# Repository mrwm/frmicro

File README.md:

# frmicro
Pro Micro adaptation to a USB C male header
-

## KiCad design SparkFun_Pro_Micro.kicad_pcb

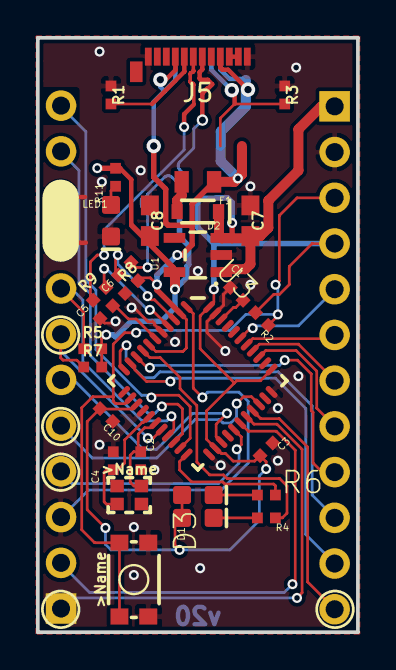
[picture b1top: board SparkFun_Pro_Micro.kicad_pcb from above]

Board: 2 copper layers, 17.8 x 33.0 mm, 35 parts (0 on the bottom side), 38 nets.

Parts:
C1, C3: 0.1uF; 0402-TIGHT
C2, C4: 22pF; 0402-TIGHT
C5, C6, C10: 1.0uF; 0402-TIGHT
C7, C8: 10uF; 0603
D1: Yellow; LED-0603
D2: 3A/10V/280mV; SOD-323
D3: GREEN; LED-0603
F1: 6V 0.5A; 0805
FRAME1: FRAME-LETTER; CREATIVE_COMMONS
J3, J4: CONN_12CASTLE; PinSocket_1x12_P2.54mm_Vertical
J5: USB_C5; USB_C_Plug_Molex_105444
JP4: JUMPER-SMT_3_1-NC_TRACE_SILK; SMT-JUMPER_3_1-NC_TRACE_SILK
LED1: RED; LED-0603
LOGO5: SPECIAL_INSTRUCTIONS-ORDERING; ORDERING_INSTRUCTIONS
R1, R3: 5.1k; 0402-TIGHT
R2: 10k; 0402-TIGHT
R4, R6, R11: 1k; 0402-TIGHT
R5, R7: 2.2k; 0402-TIGHT
R8, R9: 22OHM-0402T-1/16W-1%; 0402-TIGHT
S1: Reset; TACTILE_SWITCH_SMD_4.6X2.8MM
U1: 3.3V; SOT23-5
U3: 32U4; QFN-44-NOPAD_1_1-LESS_PASTE
U$3: OSHW-LOGOMINI; OSHW-LOGO-MINI
Y2: 16MHz; CRYSTAL-SMD-2.0X1.6MM

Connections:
3.3V: C8.2, JP4.1, R5.2, R7.2, R11.2, U1.5
/A0: J4.8, U3.36
/A1: J4.7, U3.37
/A2: J4.6, U3.38
/A3: J4.5, U3.39
/AREF: C1.2, U3.42
/D2/SDA: J3.8, R5.1, U3.19
/D3/SCL: J3.7, R7.1, U3.18
/D4: J3.6, U3.25
/D5: J3.5, U3.31
/D6: J3.4, U3.27
/D7: J3.3, U3.1
/D8: J3.2, U3.28
/D9: J3.1, U3.29
/D10: J4.12, U3.30
/D+: J5.A6, R9.1, R9.2, U3.4
/D-: J5.A7, R8.1, R8.2, U3.3
/MISO: J4.10, U3.11
/MOSI: J4.11, U3.10
/RAW: C7.2, D2.C, J4.1, JP4.3, U1.1, U1.3
/RESET: J4.3, R2.1, S1.3, S1.4, U3.13
/RXI: J3.11, U3.20
/SCK: J4.9, U3.9
/TXO: J3.12, U3.21
/UCAP: C5.2, U3.6
GND: C1.1, C2.2, C3.1, C4.2, C5.1, C6.1, C7.1, C8.1, C10.1, J3.9, J3.10, J4.2, J5.A1, J5.A12, J5.B1, J5.B12, LED1.C, R1.1, R3.1, S1.1, S1.2, U1.2, U3.5, U3.15, U3.23, U3.33, U3.35, U3.43
unnamed: C2.1, U3.17, Y2.3
unnamed: C4.1, U3.16, Y2.1
unnamed: D1.C, R4.2
unnamed: D2.A, F1.2
unnamed: D3.C, R6.2
unnamed: J5.A5, R1.2
unnamed: J5.B5, R3.2
unnamed: LED1.A, R11.1
unnamed: R4.1, U3.8
unnamed: R6.1, U3.22
VCC: C3.2, C10.2, D1.A, D3.A, J4.4, JP4.2, R2.2, U3.14, U3.24, U3.34, U3.44
V_USB: C6.2, F1.1, J5.A4, J5.A9, J5.B4, J5.B9, U3.2, U3.7

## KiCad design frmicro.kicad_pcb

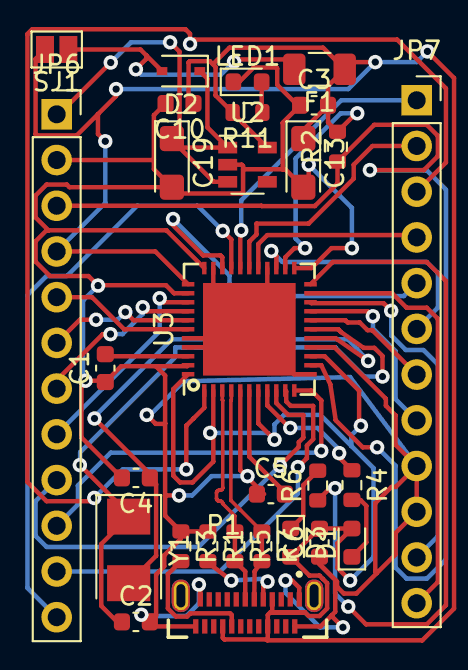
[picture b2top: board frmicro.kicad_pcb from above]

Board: 2 copper layers, 29 parts (0 on the bottom side), 36 nets.

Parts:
C1, C3: 0.1uF; C_0603_1608Metric
C2, C4: 22pF; C_0603_1608Metric
C5, C6, C10: 1uF; C_0603_1608Metric
C13, C19: 10uF; CP_EIA-3216-18_Kemet-A
D1: Yellow; LED_0603_1608Metric
D2: DIODESOD; D_SOD-323
D3: Green; LED_0603_1608Metric
F1: 500mA; Fuse_1206_3216Metric
JP6, JP7: M12PTH; PinSocket_1x12_P2.54mm_Vertical
LED1: Red; LED_0603_1608Metric
P1: USB_C_Plug; GCT_USB4155-03-C_REVA
R1, R3, R5, R7: 22; R_0603_1608Metric
R2: 10K; R_0603_1608Metric
R4, R6: 330; R_0603_1608Metric
R11: 1K; R_0603_1608Metric
SJ1: Closed for 5V Board; SolderJumper-2_P1.3mm_Open_Pad1.0x1.5mm
U2: MIC5219; SOT-23-5
U3: ATMEGA32U4; QFN-44-1EP_7x7mm_Pitch0.5mm
Y1: 16MHz; Crystal_SMD_5032-2Pin_5.0x3.2mm

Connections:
3.3V: C3.2, C6.2, C10.1, C13.1, D1.2, D3.2, F1.1, JP6.4, P1.A4, P1.A9, P1.B4, P1.B9, R2.2, R11.2, SJ1.2, U2.5, U3.2, U3.7, U3.14, U3.24, U3.34, U3.44
/A0: JP6.8, U3.36
/A1: JP6.7, U3.37
/A2: JP6.6, U3.38
/A3: JP6.5, U3.39
/AREF: C1.2, U3.42
/D2: JP7.8, U3.19
/D3: JP7.7, U3.18
/D4: JP7.6, U3.25
/D5: JP7.5, U3.31
/D6: JP7.4, U3.27
/D7: JP7.3, U3.1
/D8: JP7.2, U3.28
/D9: JP7.1, U3.29
/D10: JP6.12, U3.30
/D14: R4.1, U3.8
/D+: P1.A6, R7.1, R7.2, U3.4
/D-: P1.A7, R5.1, R5.2, U3.3
/MISO: JP6.10, U3.11
/MOSI: JP6.11, U3.10
/RAW: C19.1, D2.1, JP6.1, U2.1, U2.3
/RESET: JP6.3, R2.1, U3.13
/RXI: JP7.11, U3.20
/SCK: JP6.9, U3.9
/TXO: JP7.12, U3.21
GND: C1.1, C2.2, C3.1, C4.2, C5.1, C6.1, C10.2, C13.2, C19.2, JP6.2, JP7.9, JP7.10, LED1.1, P1.A1, P1.A12, P1.B1, P1.B12, R1.1, R3.1, U2.2, U3.5, U3.15, U3.23, U3.33, U3.35, U3.43
unnamed: C2.1, U3.17, Y1.1
unnamed: C4.1, U3.16, Y1.2
unnamed: C5.2, U3.6
unnamed: D1.1, R4.2
unnamed: D2.2, F1.2, SJ1.1
unnamed: D3.1, R6.2
unnamed: LED1.2, R11.1
unnamed: P1.A5, R1.2
unnamed: P1.B5, R3.2
unnamed: R6.1, U3.22

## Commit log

2021-09-26 initialization of kicad
2021-09-26 MCU zone completion
2021-09-26 add usb-c 2.0 connector
2021-09-26 ignore the misc folder where I third party libraries
2021-09-26 add pcb footprints and add links to readme
2021-09-26 change usb c connector and add connectors
2021-09-27 add pro micro schematics and work from that.
2021-09-28 nuked everything and reworked decided to work with import from Pro Micro Eagle file.
2021-09-28 reattribute to the correct license
2021-09-28 Update README.md
    Remove links to parts that are unused
2021-09-29 remove old pro micro schetches
2021-09-29 add Sparkfun Qwiic model and change the usb c connector from female to male

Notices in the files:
parts and their libraries:
https://creativecommons.org/licenses/by-sa/4.0
Released under the Creative Commons Attribution Share-Alike 4.0 License
